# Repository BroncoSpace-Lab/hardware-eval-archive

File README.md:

# hardware-eval-archive

This is a new repo for us to store archived hardware evaluations! 

## Archiving a New Eval
To add your recently completed eval to this repo take the following steps: 
1. Make a new branch!
2. Add your files into a new folder with your name and the date in yyyy-mm-dd format. 
3. Make a pull reqest back to the main branch!

## Hardware Eval Instructions Reference: 
Since you're interested in leaning more towards the electronics side of things, we have an evaluation that we usually give prospective hardware engineers in our lab 1 week to complete if you would like to attempt it. For that evaluation, the task will be to create a custom microcontroller development board. The requirements are as follows:

- Design a PCB that uses an [RP2040 microcontroller](https://www.raspberrypi.com/documentation/microcontrollers/rp2040.html)
- Needs to be able to boot CircuitPython.
- Board Form Factor of no greater than 50x50mm
- Has an I2C sensor integrated (any sensor).
- JLC PCB production files completed (BOM, POS, and Gerbers generated in correct format)
- Preferably designed in KiCad (Eagle or Altium will also suffice)

We understand that PCB design is not usually taught at the university level, so it is rare to have prior experience with it. This challenge is primarily to test your ability to be technically independent and learn a new design skill quickly. Both [Digikey](https://www.youtube.com/@digikey) and [Phil's Lab](https://www.youtube.com/@PhilsLab) on YouTube have excellent beginner level PCB design tutorials. If you have the time to attempt it over the weekend that would be great, but don't worry if you need more time. A follow-up design review can be scheduled to assess how you have done, and if the design looks satisfactory, we'll go ahead and order it for you to test!

__Bonus Criteria__
- Make your board as compact as possible
- Ensure that either all of the GPIO are broken out and/or have some kind of connector system (like STEMMA QT) for wiring up additional peripherals
- Make the board look cool by adding silkscreen or soldermask art!

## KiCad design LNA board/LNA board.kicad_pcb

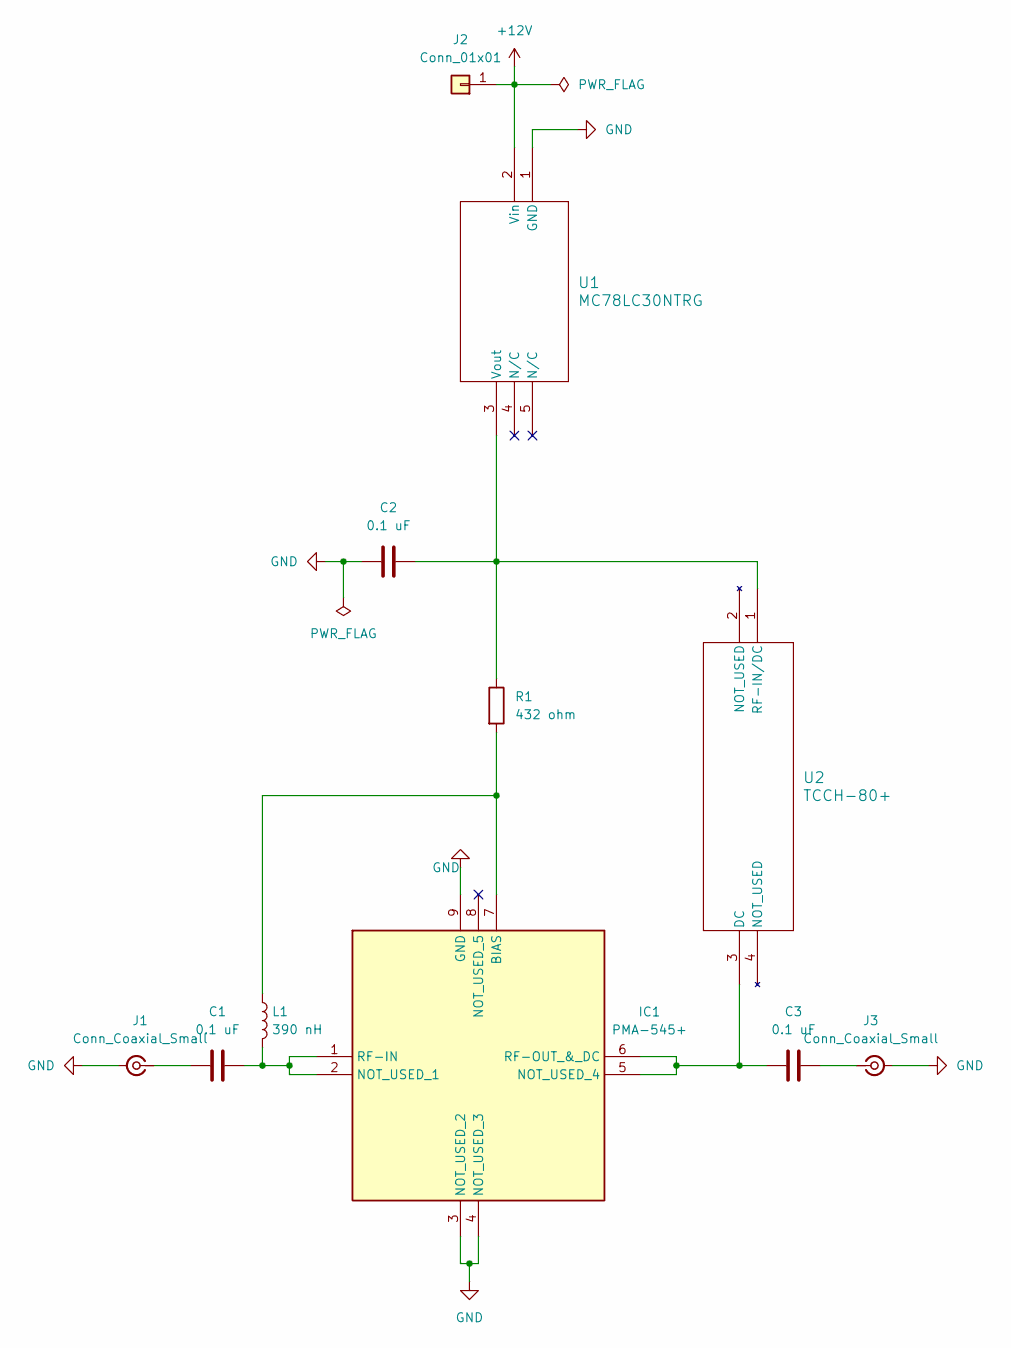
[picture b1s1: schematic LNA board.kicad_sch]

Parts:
C1, C2, C3: 0.1 uF; C_0201_0603Metric_Pad0.64x0.40mm_HandSolder
IC1: PMA-545+; PMA545; Manufacturer_Part_Number PMA-545+; Mouser Part Number 139-PMA-545
J1, J3: Conn_Coaxial_Small; SMA_Molex_73251-1153_EdgeMount_Horizontal
J2: Conn_01x01; SolderWire-2.5sqmm_1x01_D2.4mm_OD3.6mm
L1: 390 nH; L_0201_0603Metric_Pad0.64x0.40mm_HandSolder
R1: 432 ohm; R_0201_0603Metric_Pad0.64x0.40mm_HandSolder
U1: MC78LC30NTRG; TSOT23-5_ONS
U2: TCCH-80+; GU1604_MNC

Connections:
+12V: J2.1, U1.2 (Vin)
GND: C2.1, IC1.3 (NOT_USED_2), IC1.4 (NOT_USED_3), IC1.9 (GND), J1.2 (Ext), J3.2 (Ext), U1.1 (GND)
unnamed: IC1.7 (BIAS), L1.1, R1.2
unnamed: C1.2, IC1.1 (RF-IN), IC1.2 (NOT_USED_1), L1.2
unnamed: C3.1, IC1.5 (NOT_USED_4), IC1.6 (RF-OUT_&_DC), U2.3 (DC)
unnamed: C1.1, J1.1 (In)
unnamed: C3.2, J3.1 (In)
unnamed: C2.2, R1.1, U1.3 (Vout), U2.1 (RF-IN/DC)

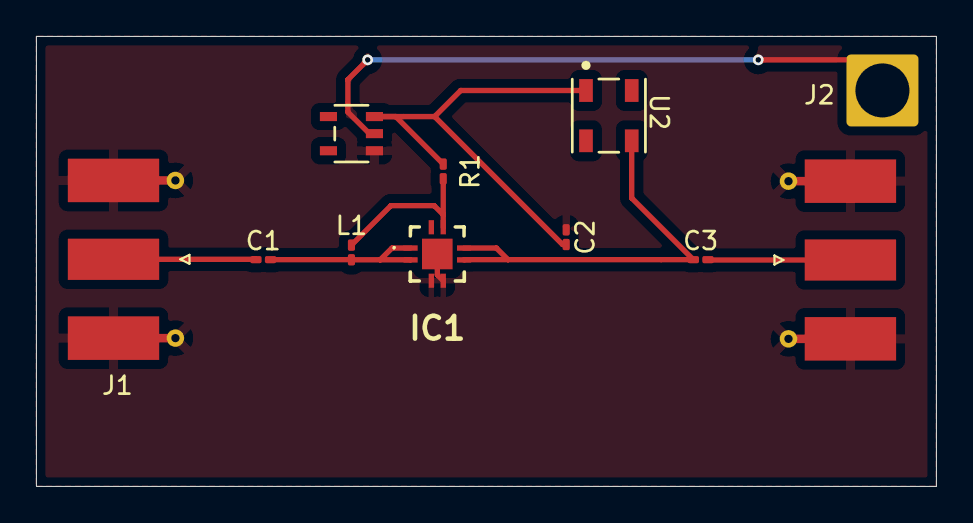
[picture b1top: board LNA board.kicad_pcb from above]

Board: 2 copper layers, 50.0 x 25.0 mm, 11 parts (0 on the bottom side), 8 nets.

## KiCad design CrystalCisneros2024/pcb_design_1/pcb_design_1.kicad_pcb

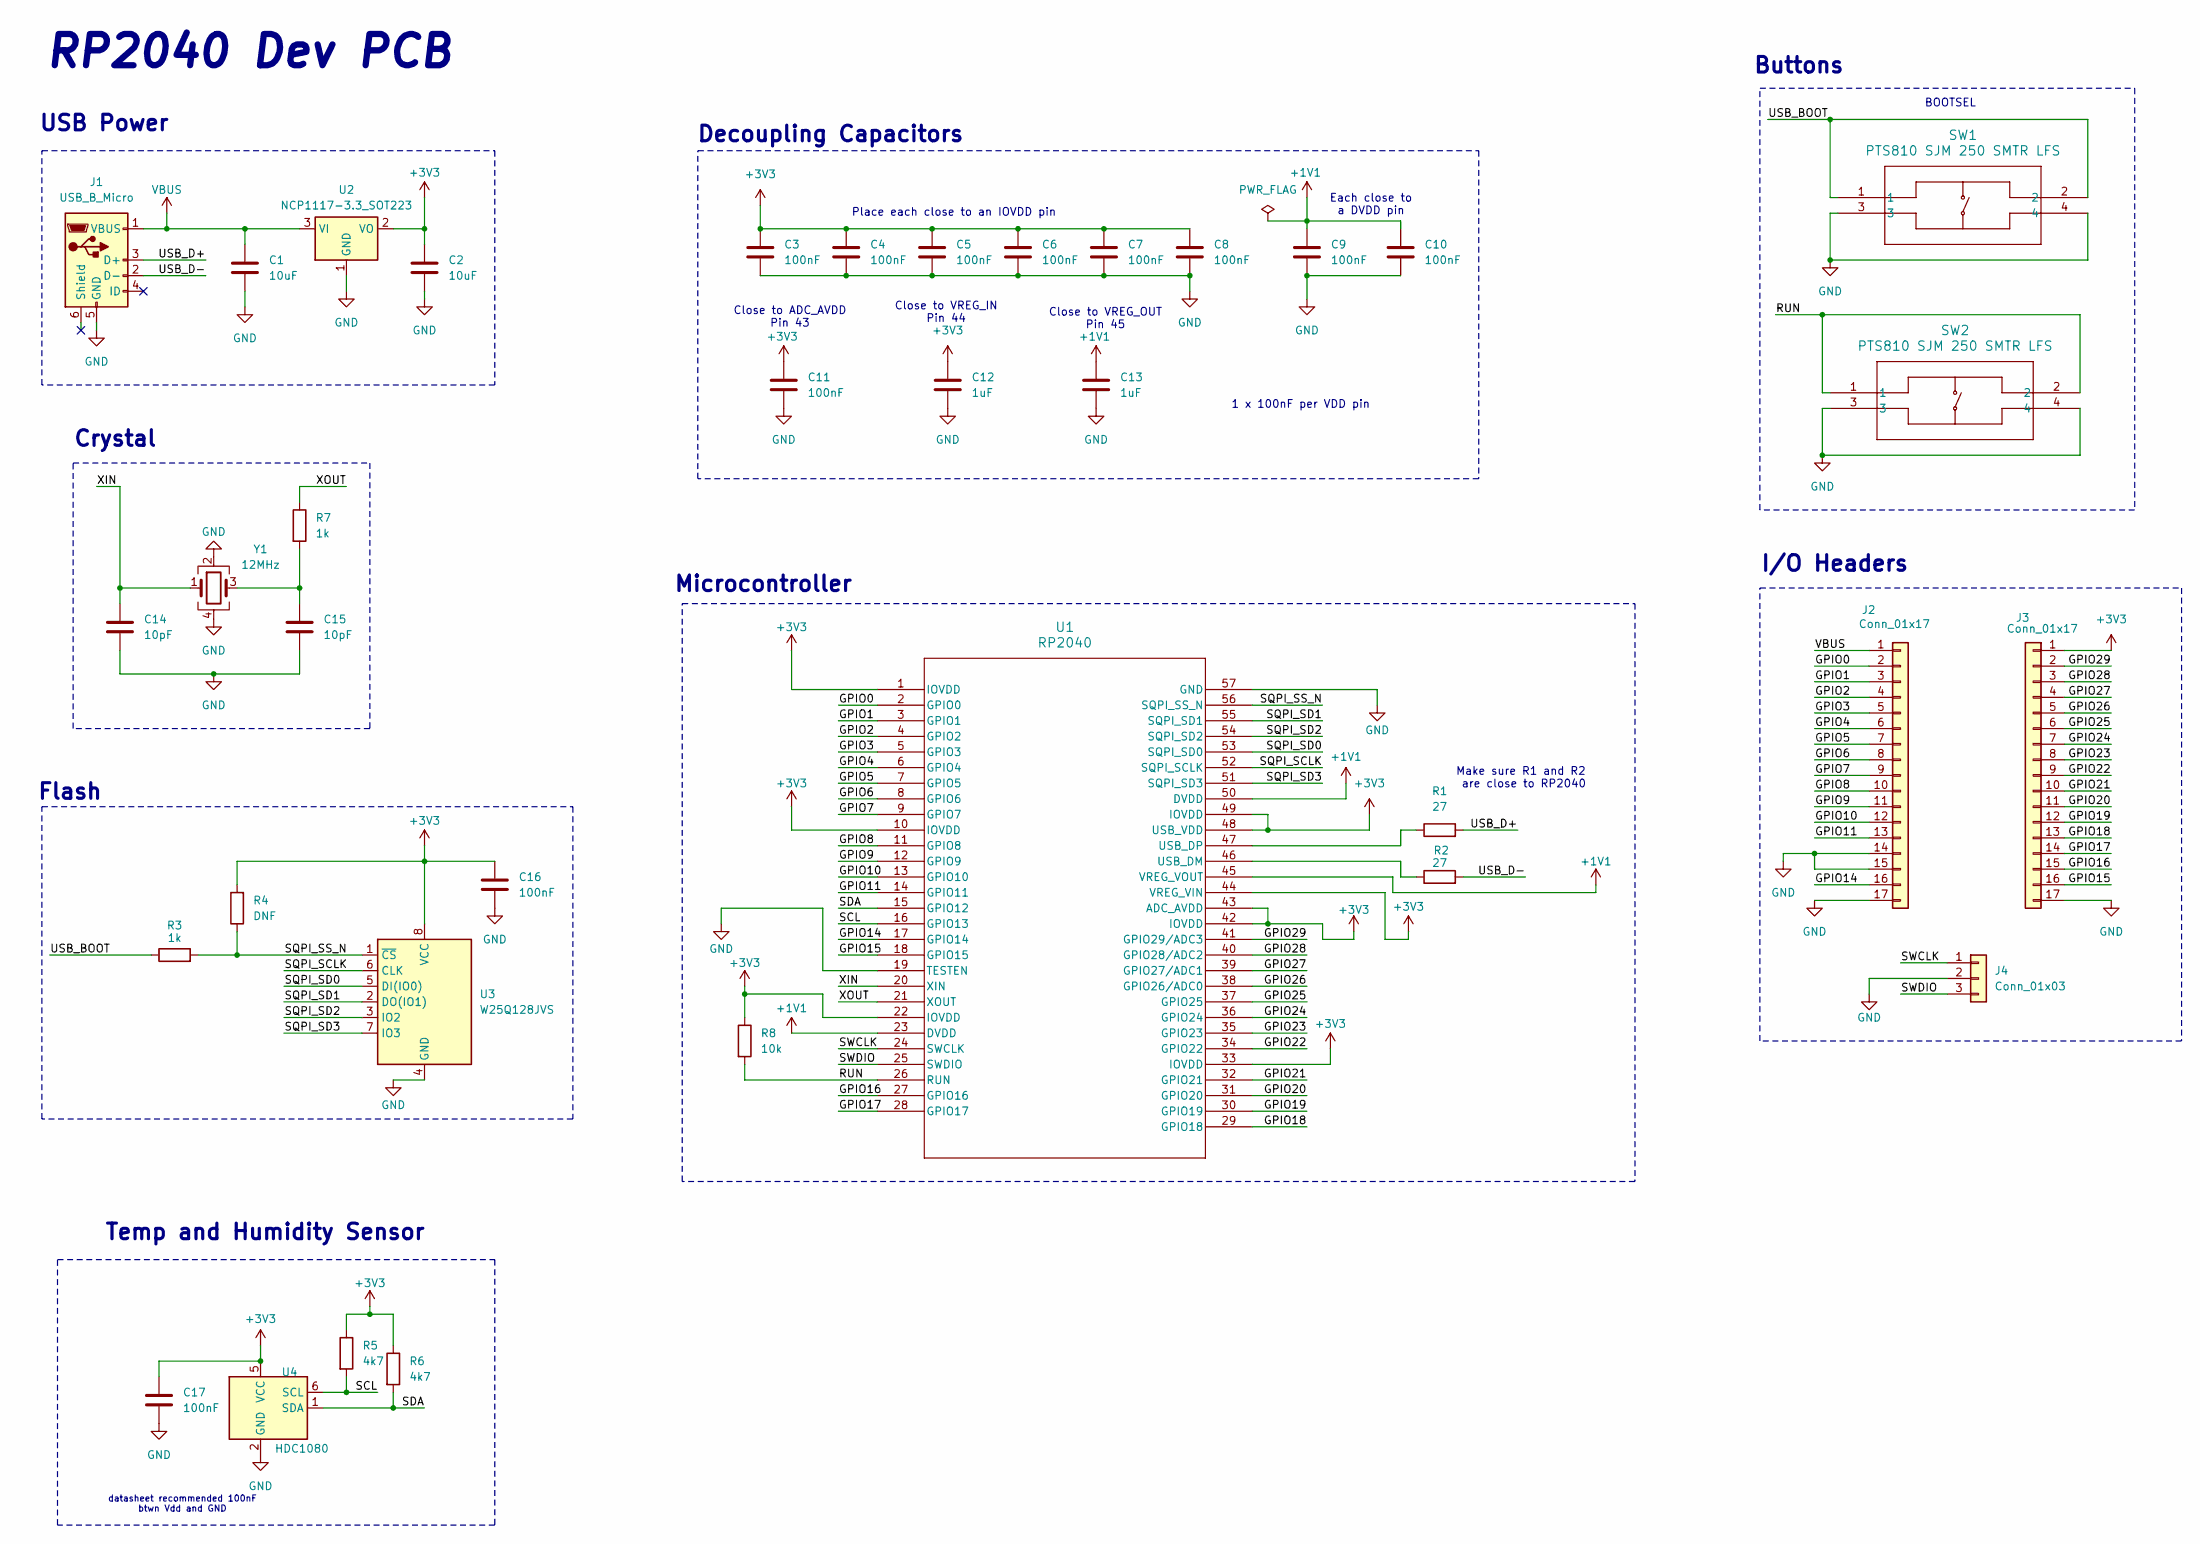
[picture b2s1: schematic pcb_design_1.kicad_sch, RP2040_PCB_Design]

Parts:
C1, C2: 10uF; C_0603_1608Metric
C3, C4, C5, C6, C7, C8, C9, C10, C11, C16, C17: 100nF; C_0402_1005Metric
C12, C13: 1uF; C_0603_1608Metric
C14, C15: 10pF; C_0402_1005Metric
J1: USB_B_Micro; USB_Micro-B_Wuerth_629105150521
J2, J3: Conn_01x17; PinHeader_1x17_P2.54mm_Vertical
J4: Conn_01x03; PinHeader_1x03_P2.54mm_Vertical
R1, R2: 27; R_0402_1005Metric
R3, R7: 1k; R_0402_1005Metric
R4: DNF; R_0402_1005Metric
R5, R6: 4k7; R_0402_1005Metric
R8: 10k; R_0402_1005Metric
SW1, SW2: PTS810 SJM 250 SMTR LFS; PTS810_CNK
U1: RP2040; QFN-56-1EP_7x7mm_P0.4mm_EP3.2x3.2mm
U2: NCP1117-3.3_SOT223; SOT-223-3_TabPin2
U3: W25Q128JVS; SOIC-8_5.23x5.23mm_P1.27mm
U4: HDC1080; Texas_PWSON-N6
Y1: 12MHz; Crystal_SMD_2520-4Pin_2.5x2.0mm

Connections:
+1V1: C9.1, C10.1, C13.1, U1.23 (DVDD), U1.45 (VREG_VOUT), U1.50 (DVDD)
+3V3: C2.1, C3.1, C4.1, C5.1, C6.1, C7.1, C8.1, C11.1, C12.1, C16.1, C17.1, J3.1, R4.2, R5.1, R6.1, R8.1, U1.1 (IOVDD), U1.10 (IOVDD), U1.22 (IOVDD), U1.33 (IOVDD), U1.42 (IOVDD), U1.43 (ADC_AVDD), U1.44 (VREG_VIN), U1.48 (USB_VDD), U1.49 (IOVDD), U2.2 (VO), U3.8 (VCC), U4.5 (VCC)
/GPIO0: J2.2, U1.2 (GPIO0)
/GPIO1: J2.3, U1.3 (GPIO1)
/GPIO2: J2.4, U1.4 (GPIO2)
/GPIO3: J2.5, U1.5 (GPIO3)
/GPIO4: J2.6, U1.6 (GPIO4)
/GPIO5: J2.7, U1.7 (GPIO5)
/GPIO6: J2.8, U1.8 (GPIO6)
/GPIO7: J2.9, U1.9 (GPIO7)
/GPIO8: J2.10, U1.11 (GPIO8)
/GPIO9: J2.11, U1.12 (GPIO9)
/GPIO10: J2.12, U1.13 (GPIO10)
/GPIO11: J2.13, U1.14 (GPIO11)
/GPIO14: J2.16, U1.17 (GPIO14)
/GPIO15: J3.16, U1.18 (GPIO15)
/GPIO16: J3.15, U1.27 (GPIO16)
/GPIO17: J3.14, U1.28 (GPIO17)
/GPIO18: J3.13, U1.29 (GPIO18)
/GPIO19: J3.12, U1.30 (GPIO19)
/GPIO20: J3.11, U1.31 (GPIO20)
/GPIO21: J3.10, U1.32 (GPIO21)
/GPIO22: J3.9, U1.34 (GPIO22)
/GPIO23: J3.8, U1.35 (GPIO23)
/GPIO24: J3.7, U1.36 (GPIO24)
/GPIO25: J3.6, U1.37 (GPIO25)
/GPIO26: J3.5, U1.38 (GPIO26/ADC0)
/GPIO27: J3.4, U1.39 (GPIO27/ADC1)
/GPIO28: J3.3, U1.40 (GPIO28/ADC2)
/GPIO29: J3.2, U1.41 (GPIO29/ADC3)
/RUN: R8.2, SW2.1, SW2.2, U1.26 (RUN)
/SCL: R5.2, U1.16 (GPIO13), U4.6 (SCL)
/SDA: R6.2, U1.15 (GPIO12), U4.1 (SDA)
/SQPI_SCLK: U1.52 (SQPI_SCLK), U3.6 (CLK)
/SQPI_SD0: U1.53 (SQPI_SD0), U3.5 (DI(IO0))
/SQPI_SD1: U1.55 (SQPI_SD1), U3.2 (DO(IO1))
/SQPI_SD2: U1.54 (SQPI_SD2), U3.3 (IO2)
/SQPI_SD3: U1.51 (SQPI_SD3), U3.7 (IO3)
/SQPI_SS_N: R3.2, R4.1, U1.56 (SQPI_SS_N), U3.1 (~CS)
/SWCLK: J4.1, U1.24 (SWCLK)
/SWDIO: J4.3, U1.25 (SWDIO)
/USB_BOOT: R3.1, SW1.1, SW1.2
/USB_D+: J1.3 (D+), R1.2
/USB_D-: J1.2 (D-), R2.2
/XIN: C14.1, U1.20 (XIN), Y1.1
/XOUT: R7.1, U1.21 (XOUT)
GND: C1.2, C2.2, C3.2, C4.2, C5.2, C6.2, C7.2, C8.2, C9.2, C10.2, C11.2, C12.2, C13.2, C14.2, C15.2, C16.2, C17.2, J1.5 (GND), J2.14, J2.15, J2.17, J3.17, J4.2, SW1.3, SW1.4, SW2.3, SW2.4, U1.19 (TESTEN), U1.57 (GND), U2.1 (GND), U3.4 (GND), U4.2 (GND), Y1.2, Y1.4
unnamed: C15.1, R7.2, Y1.3
unnamed: R2.1, U1.46 (USB_DM)
unnamed: R1.1, U1.47 (USB_DP)
VBUS: C1.1, J1.1 (VBUS), J2.1, U2.3 (VI)

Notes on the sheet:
1 x 100nF per VDD pin
Microcontroller
Flash
Make sure R1 and R2 are close to RP2040
Crystal
Close to VREG_OUT Pin 45
I/O Headers
Decoupling Capacitors
Close to ADC_AVDD Pin 43
BOOTSEL
Place each close to an IOVDD pin
Close to VREG_IN Pin 44
RP2040 Dev PCB
Each close to a DVDD pin
Buttons
datasheet recommended 100nF btwn Vdd and GND
Temp and Humidity Sensor
USB Power

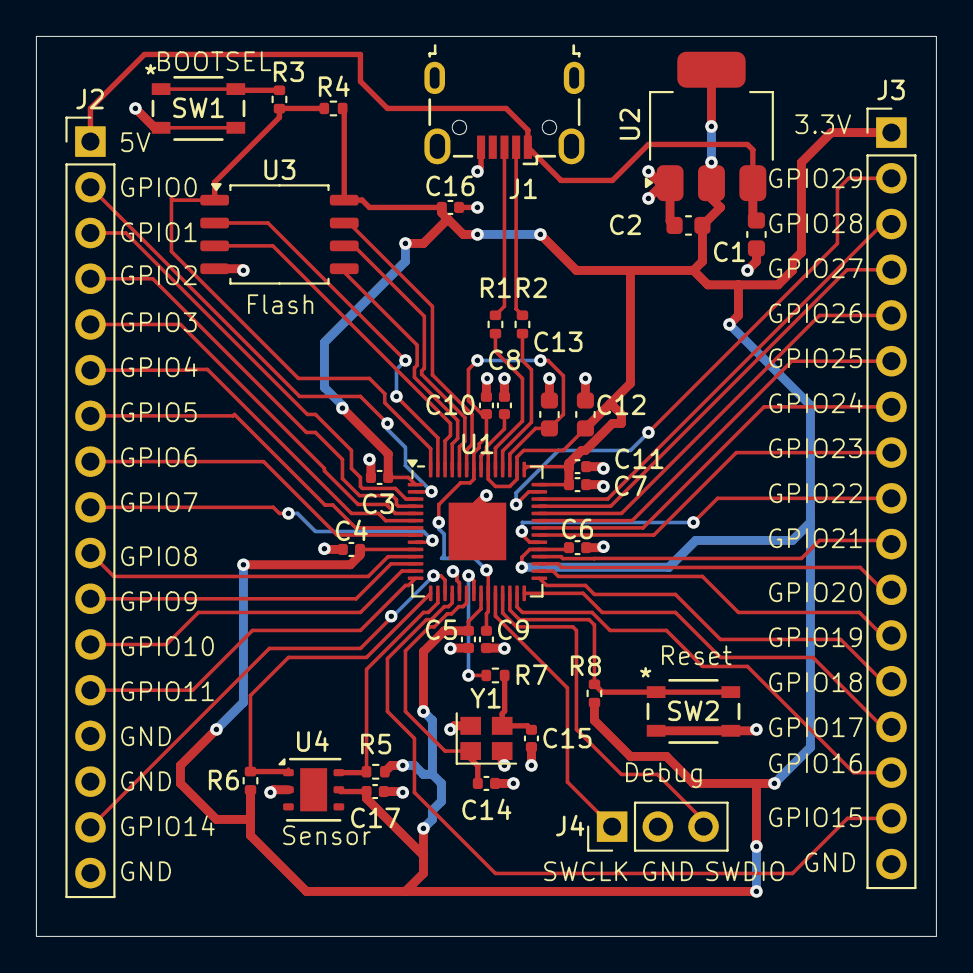
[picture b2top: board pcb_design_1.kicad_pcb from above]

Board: 2 copper layers, 50.0 x 50.0 mm, 36 parts (0 on the bottom side), 51 nets.

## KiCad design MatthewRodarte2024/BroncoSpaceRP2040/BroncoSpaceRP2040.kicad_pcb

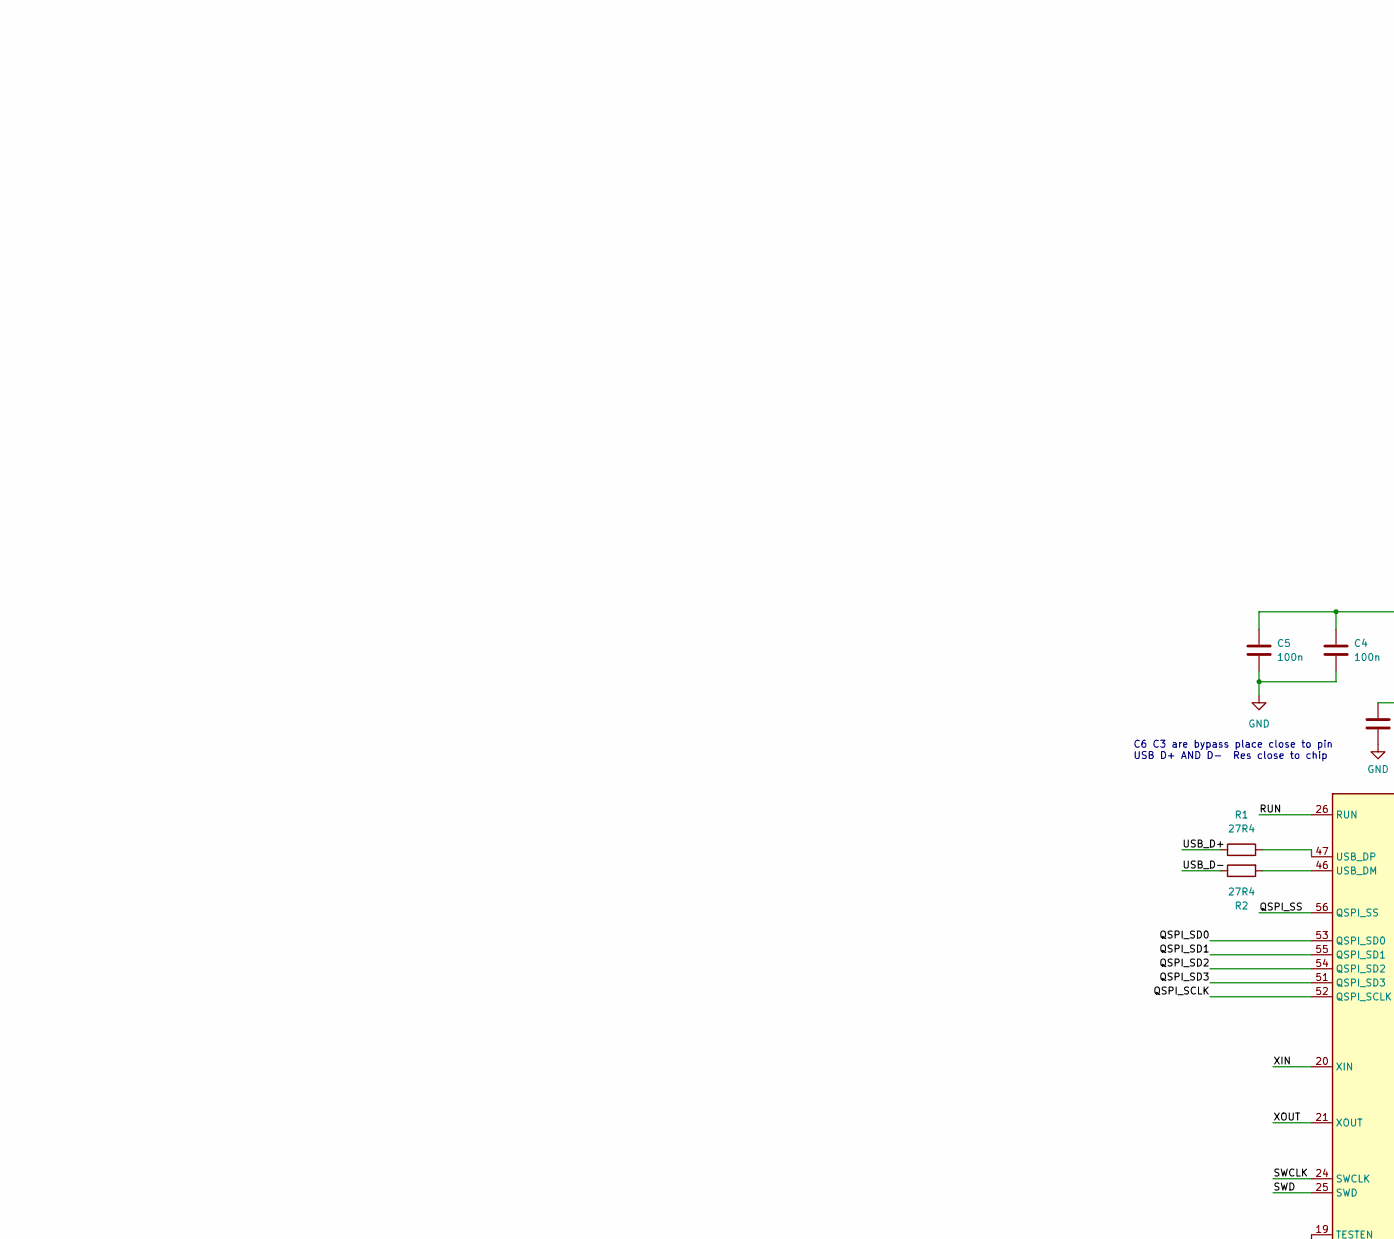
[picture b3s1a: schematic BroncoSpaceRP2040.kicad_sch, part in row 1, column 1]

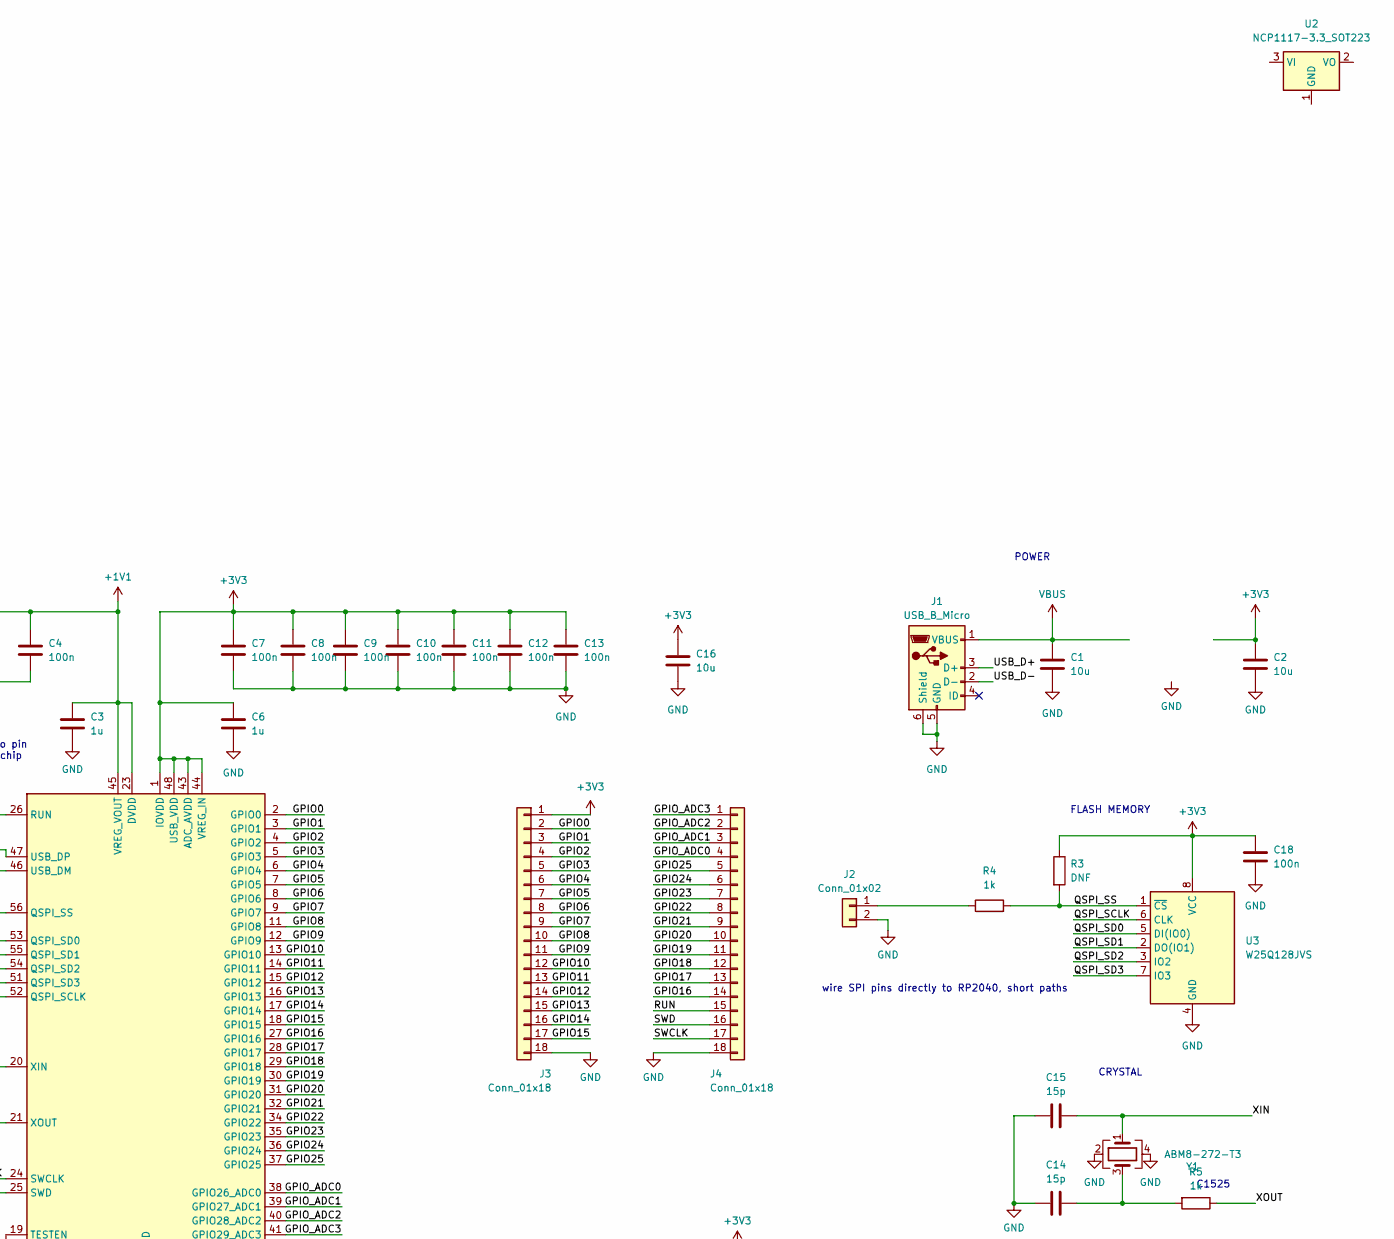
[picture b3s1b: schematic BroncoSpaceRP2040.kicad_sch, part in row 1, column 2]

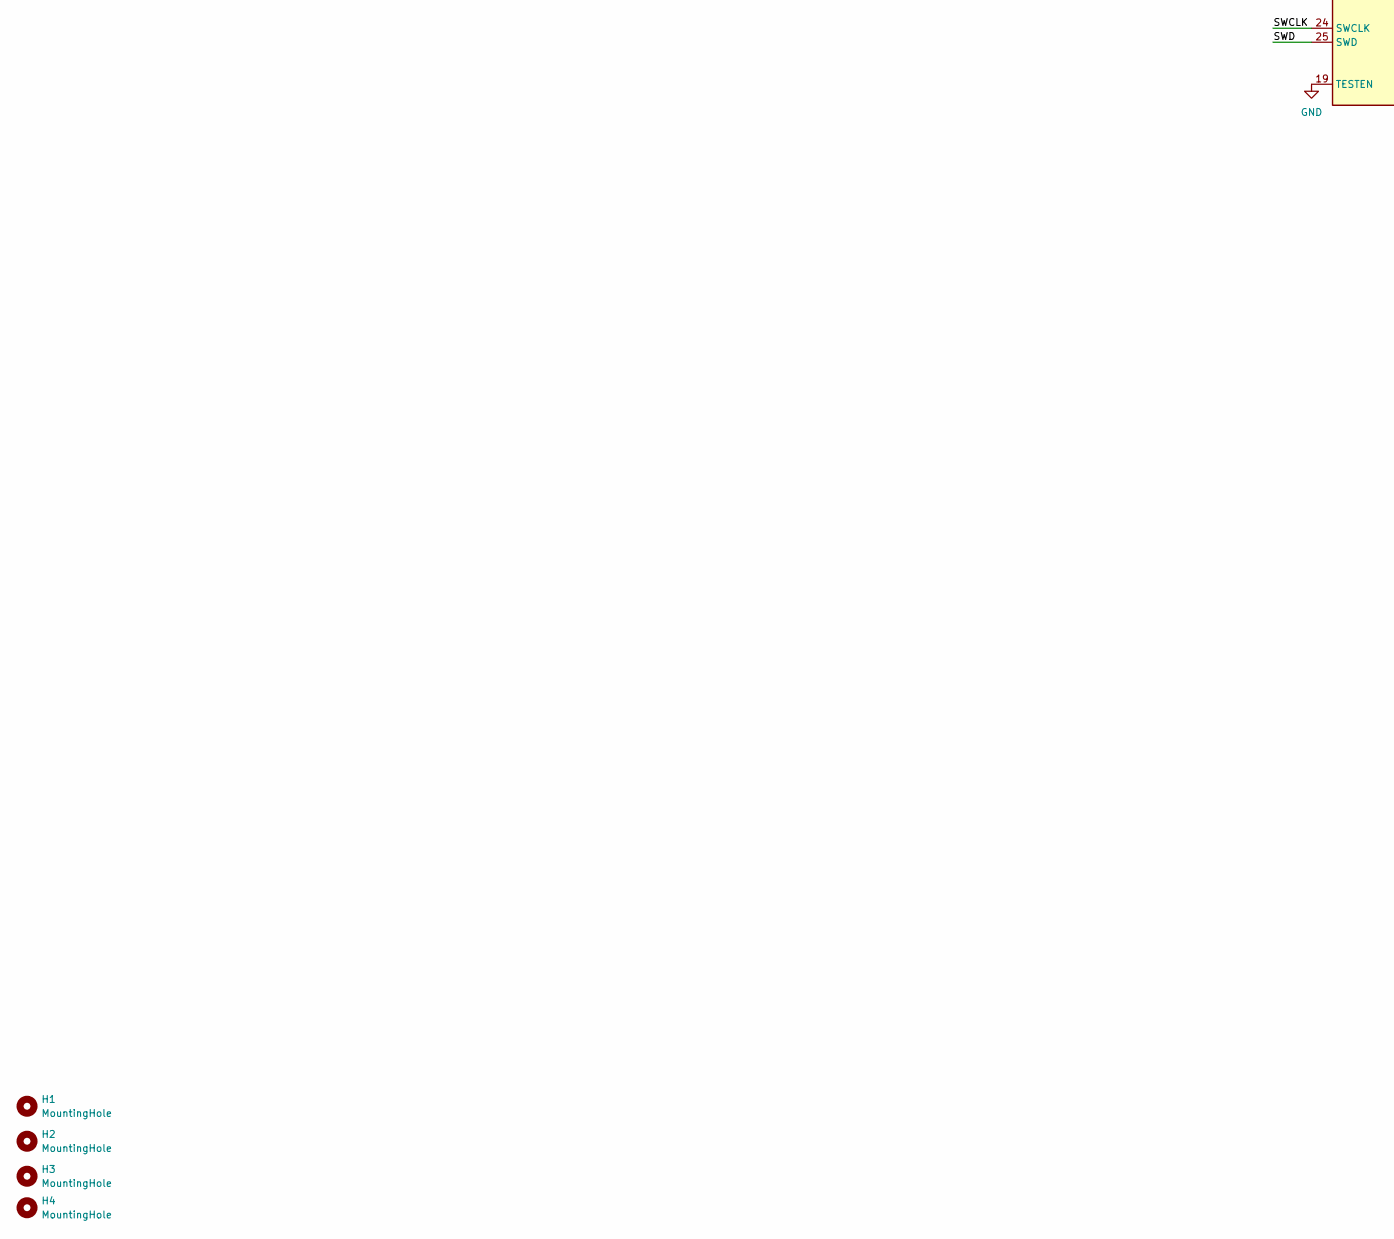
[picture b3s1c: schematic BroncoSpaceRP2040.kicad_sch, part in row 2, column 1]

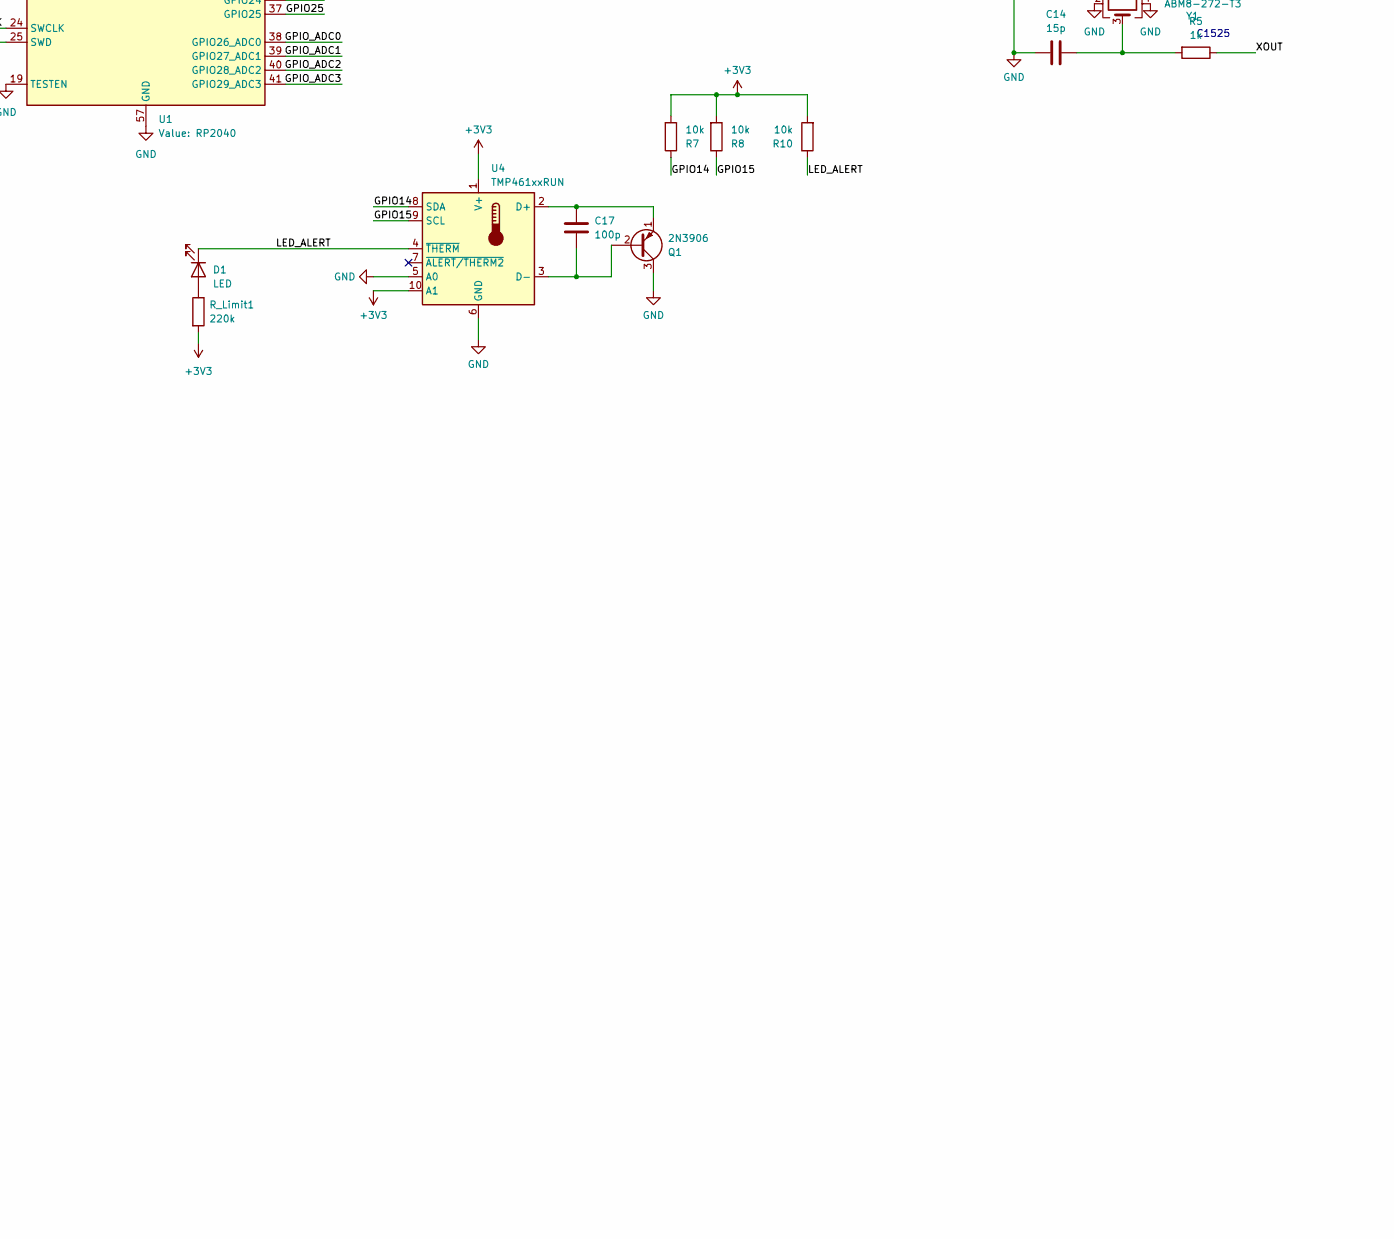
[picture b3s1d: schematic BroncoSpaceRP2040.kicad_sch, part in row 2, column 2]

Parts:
C1, C2: 10u; C_0805_2012Metric; LCSC C1046
C3, C6: 1u; C_0402_1005Metric; LCSC C29266
C4, C5, C7, C8, C9, C10, C11, C12, C13, C18: 100n; C_0402_1005Metric; LCSC C1525
C14, C15: 15p; C_0402_1005Metric; LCSC C1794
C16: 10u; C_0402_1005Metric; LCSC C1046
C17: 100p; C_0402_1005Metric; LCSC C26409
D1: LED; LED_D3.0mm; LCSC C10679
H1, H2, H3, H4: MountingHole; MountingHole_2.7mm_M2.5
J1: USB_B_Micro; USB_Micro-B_Amphenol_10103594-0001LF_Horizontal; LCSC C2681556
J2: Conn_01x02; PinHeader_1x02_P2.54mm_Vertical; LCSC C2905434
J3, J4: Conn_01x18; PinHeader_1x18_P2.54mm_Vertical; LCSC C5142873
Q1: 2N3906; TO-92_Inline; LCSC C124483
R1, R2: 27R4; R_0402_1005Metric; LCSC C172043
R3: DNF; R_0402_1005Metric
R4, R5: 1k; R_0402_1005Metric; LCSC C1525
R7, R8, R10: 10k; R_0402_1005Metric; LCSC C1525
R_Limit1: 220k; R_0805_2012Metric
U1: RP2040; QFN-56-1EP_7x7mm_P0.4mm_EP3.2x3.2mm; LCSC C2040
U2: NCP1117-3.3_SOT223; SOT-223-3_TabPin2; LCSC C26537
U3: W25Q128JVS; SOIC-8_5.23x5.23mm_P1.27mm; LCSC C97521
U4: TMP461xxRUN; Texas_WQFN-10_2x2mm_P0.5mm; LCSC C2873234
Y1: ABM8-272-T3; Crystal_SMD_3225-4Pin_3.2x2.5mm; LCSC C20625731

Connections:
+1V1: C3.1, C4.1, C5.1, U1.23 (DVDD), U1.45 (VREG_VOUT), U1.50 (DVDD)
+3V3: C2.1, C6.1, C7.1, C8.1, C9.1, C10.1, C11.1, C12.1, C13.1, C16.1, C18.1, J3.1, R3.1, R7.2, R8.2, R10.2, R_Limit1.2, U1.1 (IOVDD), U1.10 (IOVDD), U1.22 (IOVDD), U1.33 (IOVDD), U1.42 (IOVDD), U1.43 (ADC_AVDD), U1.44 (VREG_IN), U1.48 (USB_VDD), U1.49 (IOVDD), U2.2 (VO), U3.8 (VCC), U4.1 (V+), U4.10 (A1)
/GPIO0: J3.2, U1.2 (GPIO0)
/GPIO1: J3.3, U1.3 (GPIO1)
/GPIO2: J3.4, U1.4 (GPIO2)
/GPIO3: J3.5, U1.5 (GPIO3)
/GPIO4: J3.6, U1.6 (GPIO4)
/GPIO5: J3.7, U1.7 (GPIO5)
/GPIO6: J3.8, U1.8 (GPIO6)
/GPIO7: J3.9, U1.9 (GPIO7)
/GPIO8: J3.10, U1.11 (GPIO8)
/GPIO9: J3.11, U1.12 (GPIO9)
/GPIO10: J3.12, U1.13 (GPIO10)
/GPIO11: J3.13, U1.14 (GPIO11)
/GPIO12: J3.14, U1.15 (GPIO12)
/GPIO13: J3.15, U1.16 (GPIO13)
/GPIO14: J3.16, R7.1, U1.17 (GPIO14), U4.8 (SDA)
/GPIO15: J3.17, R8.1, U1.18 (GPIO15), U4.9 (SCL)
/GPIO16: J4.14, U1.27 (GPIO16)
/GPIO17: J4.13, U1.28 (GPIO17)
/GPIO18: J4.12, U1.29 (GPIO18)
/GPIO19: J4.11, U1.30 (GPIO19)
/GPIO20: J4.10, U1.31 (GPIO20)
/GPIO21: J4.9, U1.32 (GPIO21)
/GPIO22: J4.8, U1.34 (GPIO22)
/GPIO23: J4.7, U1.35 (GPIO23)
/GPIO24: J4.6, U1.36 (GPIO24)
/GPIO25: J4.5, U1.37 (GPIO25)
/GPIO_ADC0: J4.4, U1.38 (GPIO26_ADC0)
/GPIO_ADC1: J4.3, U1.39 (GPIO27_ADC1)
/GPIO_ADC2: J4.2, U1.40 (GPIO28_ADC2)
/GPIO_ADC3: J4.1, U1.41 (GPIO29_ADC3)
/LED_ALERT: D1.1 (K), R10.1, U4.4 (~THERM)
/QSPI_SCLK: U1.52 (QSPI_SCLK), U3.6 (CLK)
/QSPI_SD0: U1.53 (QSPI_SD0), U3.5 (DI(IO0))
/QSPI_SD1: U1.55 (QSPI_SD1), U3.2 (DO(IO1))
/QSPI_SD2: U1.54 (QSPI_SD2), U3.3 (IO2)
/QSPI_SD3: U1.51 (QSPI_SD3), U3.7 (IO3)
/QSPI_SS: R3.2, R4.2, U1.56 (QSPI_SS), U3.1 (~CS)
/RUN: J4.15, U1.26 (RUN)
/SWCLK: J4.17, U1.24 (SWCLK)
/SWD: J4.16, U1.25 (SWD)
/USB_D+: J1.3 (D+), R1.1
/USB_D-: J1.2 (D-), R2.1
/XIN: C15.1, U1.20 (XIN), Y1.1
/XOUT: R5.1, U1.21 (XOUT)
GND: C1.2, C2.2, C3.2, C4.2, C5.2, C6.2, C7.2, C8.2, C9.2, C10.2, C11.2, C12.2, C13.2, C14.2, C15.2, C16.2, C18.2, J1.5 (GND), J1.6 (Shield), J2.2, J3.18, J4.18, Q1.3 (C), U1.19 (TESTEN), U1.57 (GND), U2.1 (GND), U3.4 (GND), U4.5 (A0), U4.6 (GND), Y1.2, Y1.4
unnamed: C14.1, R5.2, Y1.3
unnamed: D1.2 (A), R_Limit1.1
unnamed: J2.1, R4.1
unnamed: C17.2, Q1.2 (B), U4.3 (D-)
unnamed: C17.1, Q1.1 (E), U4.2 (D+)
unnamed: R2.2, U1.46 (USB_DM)
unnamed: R1.2, U1.47 (USB_DP)
VBUS: C1.1, J1.1 (VBUS), U2.3 (VI)

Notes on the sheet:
POWER
FLASH MEMORY
C1525
CRYSTAL
wire SPI pins directly to RP2040, short paths
C6 C3 are bypass place close to pin USB D+ AND D- Res close to chip

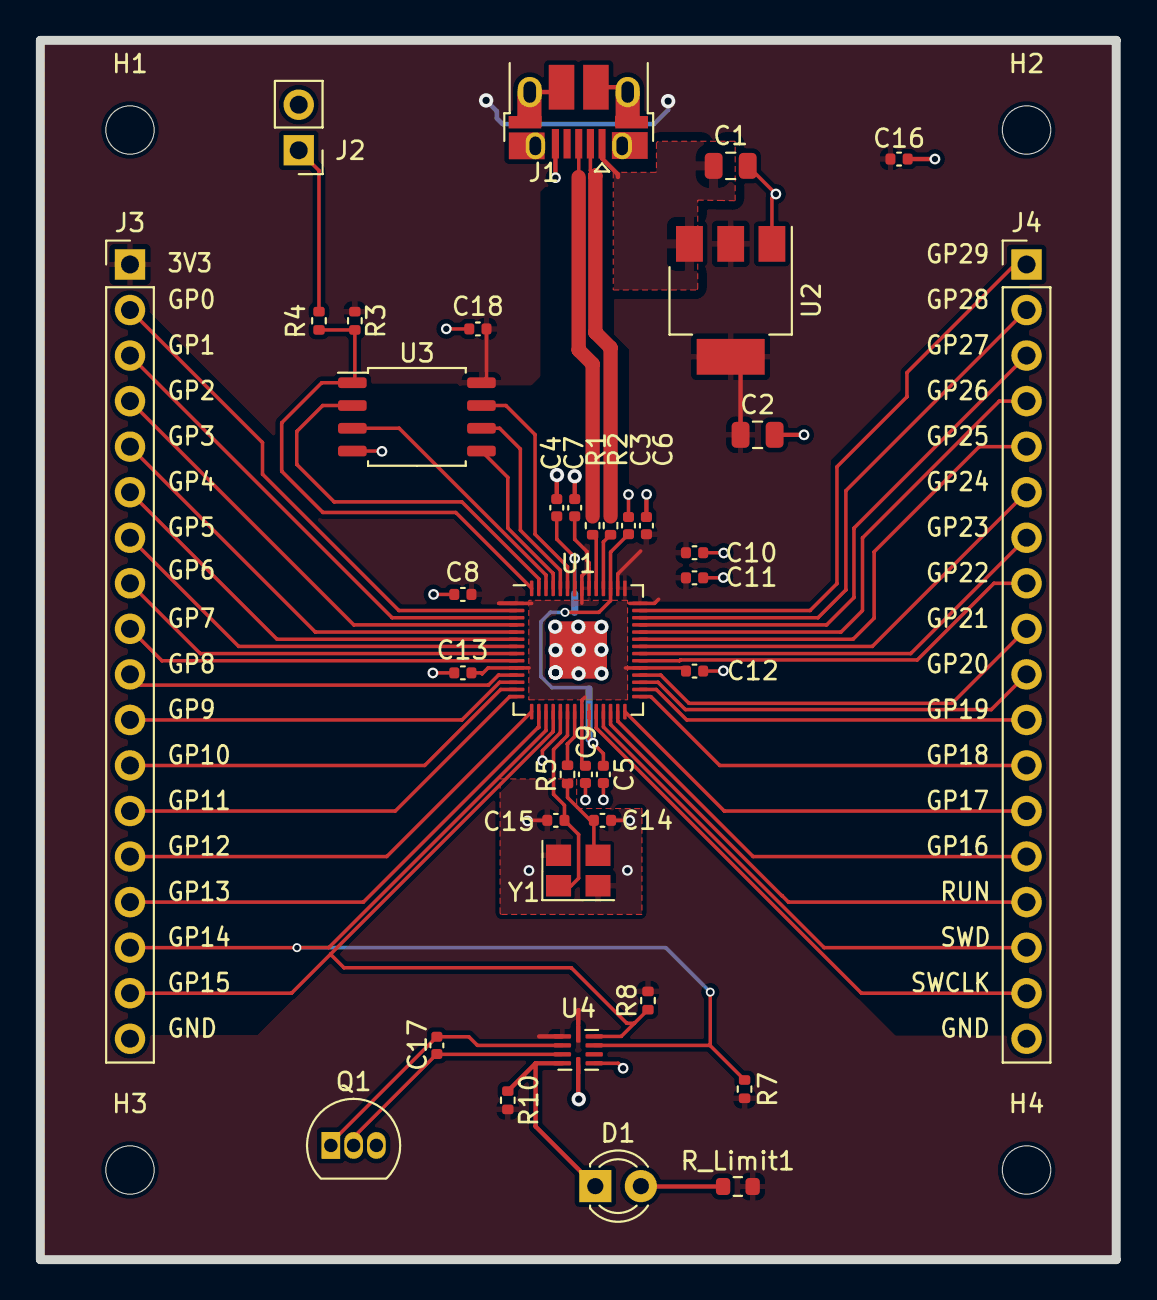
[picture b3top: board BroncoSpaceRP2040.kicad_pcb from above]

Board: 2 copper layers, 60.0 x 68.0 mm, 42 parts (0 on the bottom side), 55 nets.

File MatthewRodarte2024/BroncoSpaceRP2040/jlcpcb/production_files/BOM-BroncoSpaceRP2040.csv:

Comment,Designator,Footprint,LCSC
10u,"C1,C16,C2",C_0805_2012Metric,C1046
1k,"R4,R5",R_0402_1005Metric,C11702
2N3906,Q1,TO-92_Inline,C124483
100n,"C10,C11,C12,C13,C18,C4,C5,C7,C8,C9",C_0402_1005Metric,C1525
100p,C17,C_0402_1005Metric,C1546
27R4,"R1,R2",R_0402_1005Metric,C172043
15p,"C14,C15",C_0402_1005Metric,C17944
RP2040,U1,QFN-56-1EP_7x7mm_P0.4mm_EP3.2x3.2mm,C2040
ABM8-272-T3,Y1,Crystal_SMD_3225-4Pin_3.2x2.5mm,C20625731
470,R_Limit1,R_0603_1608Metric,C23179
10k,"R10,R7,R8",R_0402_1005Metric,C25744
NCP1117-3.3_SOT223,U2,SOT-223-3_TabPin2,C26537
USB_B_Micro,J1,USB_Micro-B_Amphenol_10103594-0001LF_Horizontal,C2681556
TMP461xxRUN,U4,Texas_WQFN-10_2x2mm_P0.5mm,C2873234
1u,"C3,C6",C_0402_1005Metric,C52923
W25Q128JVS,U3,SOIC-8_5.23x5.23mm_P1.27mm,C97521
MountingHole,H3,MountingHole_2.7mm_M2.5,
Conn_01x18,J4,PinHeader_1x18_P2.54mm_Vertical,
MountingHole,H2,MountingHole_2.7mm_M2.5,
Conn_01x02,J2,PinHeader_1x02_P2.54mm_Vertical,
MountingHole,H1,MountingHole_2.7mm_M2.5,
MountingHole,H4,MountingHole_2.7mm_M2.5,
Conn_01x18,J3,PinHeader_1x18_P2.54mm_Vertical,
LED,D1,LED_D3.0mm,
DNF,R3,R_0402_1005Metric,
